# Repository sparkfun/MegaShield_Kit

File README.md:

SparkFun MegaShield Kit
=======================

[*SparkFun MegaShield Kit (DEV-09346)*](https://www.sparkfun.com/products/9346)

 The SparkFun MegaShield mates with the Arduino Mega board and gives the user a prototyping area, two general LEDs, 
 and, most important of all, the Arduino Mega reset switch is brought to the top level.
 
Repository Contents
-------------------
* **/Hardware** - All Eagle design files (.brd, .sch)

License Information
-------------------
The hardware is released under [Creative Commons ShareAlike 4.0 International](https://creativecommons.org/licenses/by-sa/4.0/).

Distributed as-is; no warranty is given.

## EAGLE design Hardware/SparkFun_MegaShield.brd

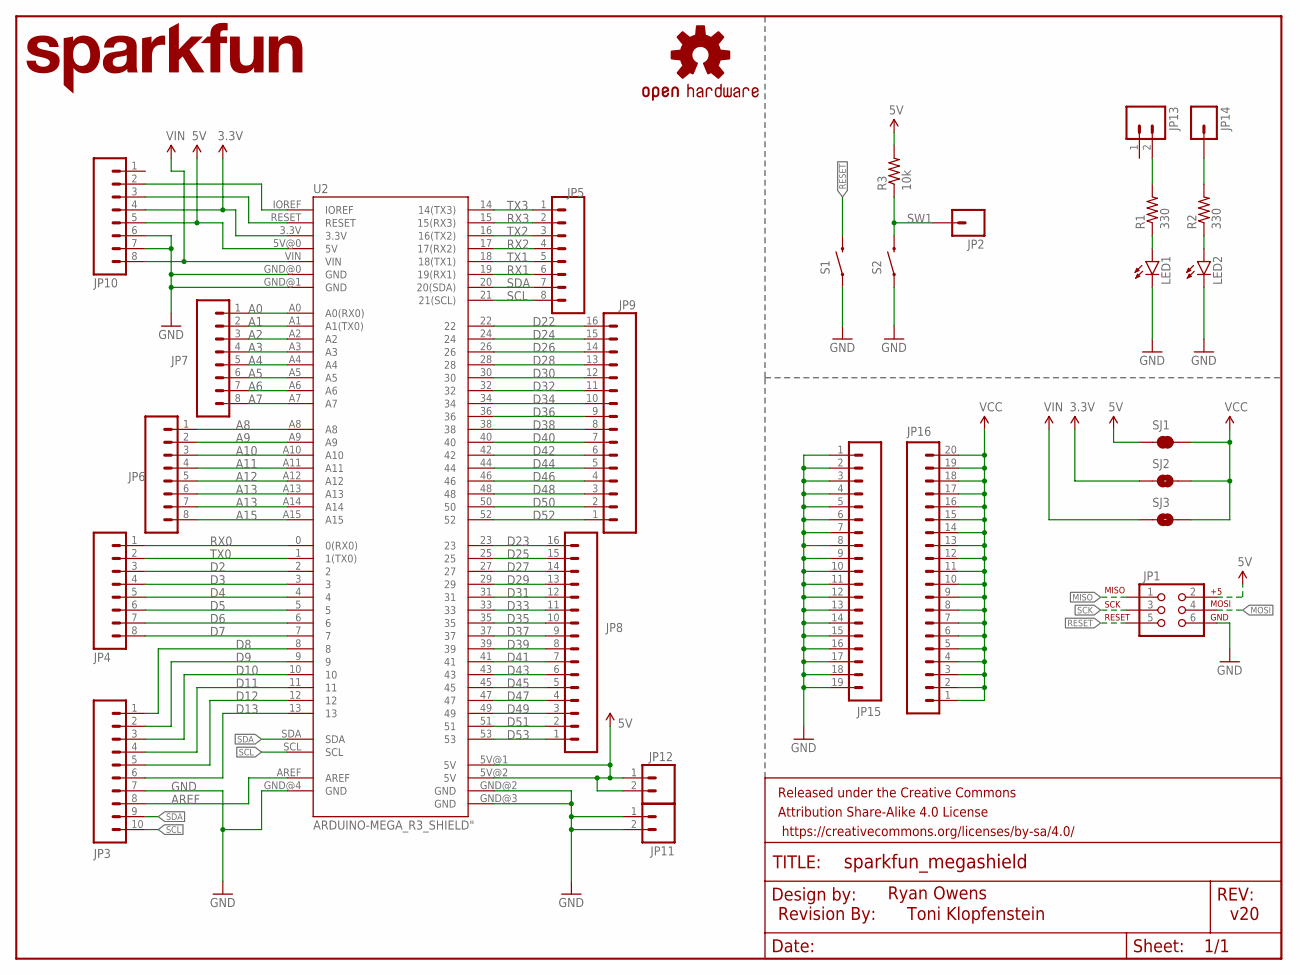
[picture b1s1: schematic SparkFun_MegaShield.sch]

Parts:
FRAME1: FRAME-LETTER; CREATIVE_COMMONS
JP1: AVR_SPI_PRG_6PTH; 2X3
JP2, JP14: M01PTH; 1X01
JP3: M10SILK_FEMALE_PTH; 1X10
JP4, JP5, JP6, JP7, JP10: M08; 1X08_ROUND
JP8, JP9: M16PTH; 1X16
JP11, JP12, JP13: M02PTH; 1X02
JP15: M191X19; 1X19
JP16: M20; 1X20
LED1: Red; LED3MM
LED2: Green; LED3MM
LOGO1: OSHW-LOGOS; OSHW-LOGO-S
LOGO2: SFE_LOGO_NAME.1_INCH; SFE_LOGO_NAME_.1
R1, R2: 330; AXIAL-0.3
R3: 10k; AXIAL-0.3
S1, S2: SWITCH-MOMENTARY-2PTH; TACTILE-PTH
SJ1: JUMPER-PAD-2-NC_BY_TRACE; PAD-JUMPER-2-NC_BY_TRACE_YES_SILK
SJ2, SJ3: JUMPER-PAD-2-NOYES_SILK; PAD-JUMPER-2-NO_YES_SILK
U2: ARDUINO-MEGA_R3_SHIELD"; ARDUINO_MEGA_R3_OUTLINE
U$3: REVISION

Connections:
3.3V: JP10.4, SJ2.1, U2.3.3V
5V: JP1.2, JP10.5, JP12.1, JP12.2, R3.P$2 (2), SJ1.1, U2.5V@0 (5V), U2.5V@1 (5V), U2.5V@2 (5V)
A0: JP7.1, U2.A0 (A0(RX0))
A1: JP7.2, U2.A1 (A1(TX0))
A2: JP7.3, U2.A2
A3: JP7.4, U2.A3
A4: JP7.5, U2.A4
A5: JP7.6, U2.A5
A6: JP7.7, U2.A6
A7: JP7.8, U2.A7
A8: JP6.1, U2.A8
A9: JP6.2, U2.A9
A10: JP6.3, U2.A10
A11: JP6.4, U2.A11
A12: JP6.5, U2.A12
A13: JP6.6, U2.A13
A14: JP6.7, U2.A14
A15: JP6.8, U2.A15
AREF: JP3.8, U2.AREF
D2: JP4.3, U2.2
D3: JP4.4, U2.3
D4: JP4.5, U2.4
D5: JP4.6, U2.5
D6: JP4.7, U2.6
D7: JP4.8, U2.7
D8: JP3.1, U2.8
D9: JP3.2, U2.9
D10: JP3.3, U2.10
D11: JP3.4, U2.11
D12: JP3.5, U2.12
D13: JP3.6, U2.13
D22: JP9.16, U2.22
D23: JP8.16, U2.23
D24: JP9.15, U2.24
D25: JP8.15, U2.25
D26: JP9.14, U2.26
D27: JP8.14, U2.27
D28: JP9.13, U2.28
D29: JP8.13, U2.29
D30: JP9.12, U2.30
D31: JP8.12, U2.31
D32: JP9.11, U2.32
D33: JP8.11, U2.33
D34: JP9.10, U2.34
D35: JP8.10, U2.35
D36: JP9.9, U2.36
D37: JP8.9, U2.37
D38: JP9.8, U2.38
D39: JP8.8, U2.39
D40: JP9.7, U2.40
D41: JP8.7, U2.41
D42: JP9.6, U2.42
D43: JP8.6, U2.43
D44: JP9.5, U2.44
D45: JP8.5, U2.45
D46: JP9.4, U2.46
D47: JP8.4, U2.47
D48: JP9.3, U2.48
D49: JP8.3, U2.49
D50: JP9.2, U2.50
D51: JP8.2, U2.51
D52: JP9.1, U2.52
D53: JP8.1, U2.53
GND: JP1.6, JP3.7, JP10.6, JP10.7, JP11.1, JP11.2, JP15.1, JP15.2, JP15.3, JP15.4, JP15.5, JP15.6, JP15.7, JP15.8, JP15.9, JP15.10, JP15.11, JP15.12, JP15.13, JP15.14, JP15.15, JP15.16, JP15.17, JP15.18, JP15.19, LED1.K (C), LED2.K (C), S1.1, S2.1, U2.GND@0 (GND), U2.GND@1 (GND), U2.GND@2 (GND), U2.GND@3 (GND), U2.GND@4 (GND)
MISO: JP1.1
MOSI: JP1.4
unnamed: LED1.A, R1.P$1 (1)
unnamed: LED2.A, R2.P$1 (1)
unnamed: JP10.2, U2.IOREF
unnamed: JP13.2, R1.P$2 (2)
unnamed: JP14.1, R2.P$2 (2)
RESET: JP1.5, JP10.3, S1.3 (2), U2.RESET
RX0: JP4.1, U2.0 (0(RX0))
RX1: JP5.6, U2.19 (19(RX1))
RX2: JP5.4, U2.17 (17(RX2))
RX3: JP5.2, U2.15 (15(RX3))
SCK: JP1.3
SCL: JP3.10, JP5.8, U2.21 (21(SCL)), U2.SCL
SDA: JP3.9, JP5.7, U2.20 (20(SDA)), U2.SDA
SW1: JP2.1, R3.P$1 (1), S2.3 (2)
TX0: JP4.2, U2.1 (1(TX0))
TX1: JP5.5, U2.18 (18(TX1))
TX2: JP5.3, U2.16 (16(TX2))
TX3: JP5.1, U2.14 (14(TX3))
VCC: JP16.1, JP16.2, JP16.3, JP16.4, JP16.5, JP16.6, JP16.7, JP16.8, JP16.9, JP16.10, JP16.11, JP16.12, JP16.13, JP16.14, JP16.15, JP16.16, JP16.17, JP16.18, JP16.19, JP16.20, SJ1.2, SJ2.2, SJ3.2
VIN: JP10.8, SJ3.1, U2.VIN

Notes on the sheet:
v20
Ryan Owens
Toni Klopfenstein

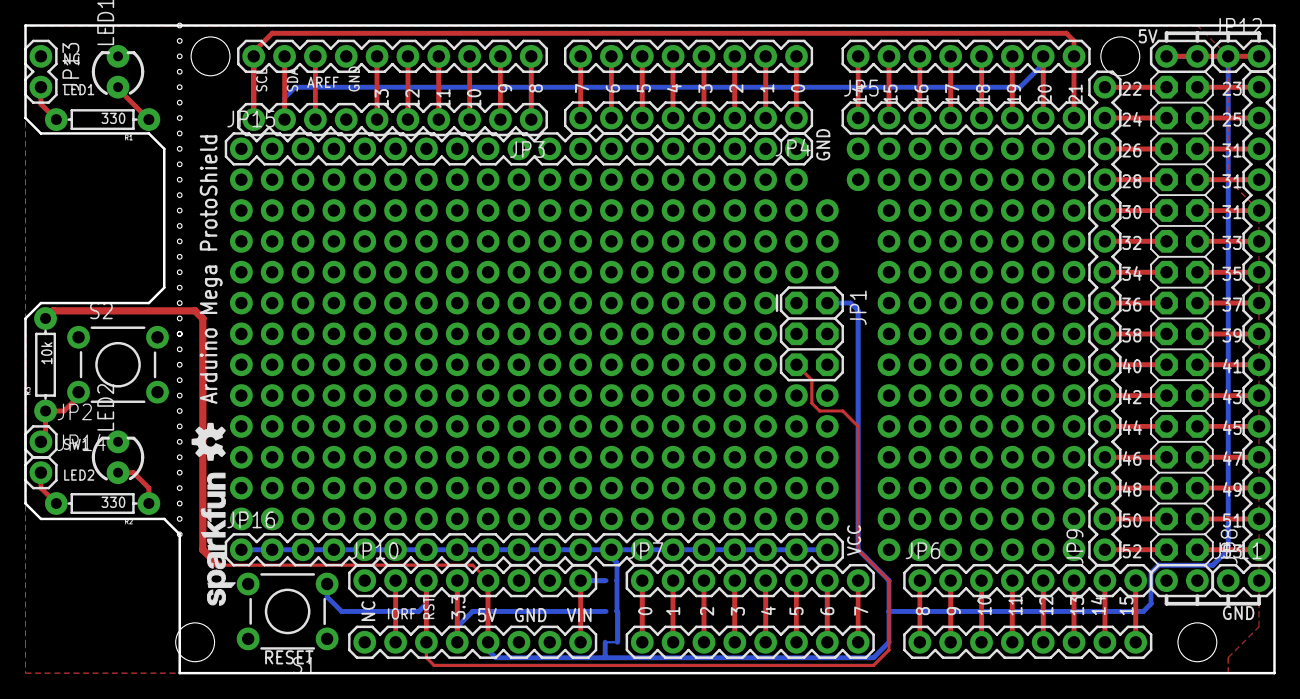
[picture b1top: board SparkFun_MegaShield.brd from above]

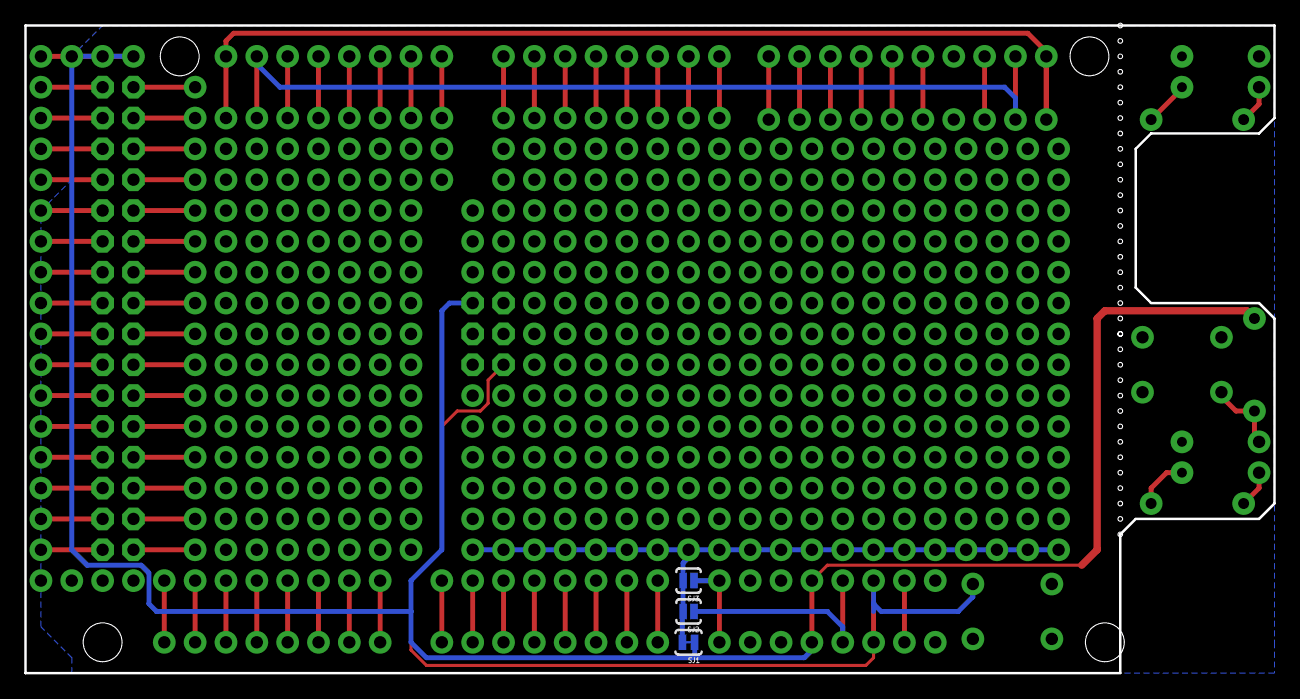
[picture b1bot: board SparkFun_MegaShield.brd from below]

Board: 2 copper layers, 102.9 x 53.3 mm, 31 parts (3 on the bottom side), 83 nets.

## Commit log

2015-03-10 Adding hardware files, updating README
2015-09-03 Initial rev changes - WIP
2015-09-04 Ready for first review

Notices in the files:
parts and their libraries:
SparkFun-Aesthetics: Licensing: Creative Commons ShareAlike 4.0 International - https://creativecommons.org/licenses/by-sa/4.0
SparkFun-Aesthetics: Released under the Creative Commons Attribution Share-Alike 4.0 License
SparkFun-Aesthetics: Released under the Creative Commons
